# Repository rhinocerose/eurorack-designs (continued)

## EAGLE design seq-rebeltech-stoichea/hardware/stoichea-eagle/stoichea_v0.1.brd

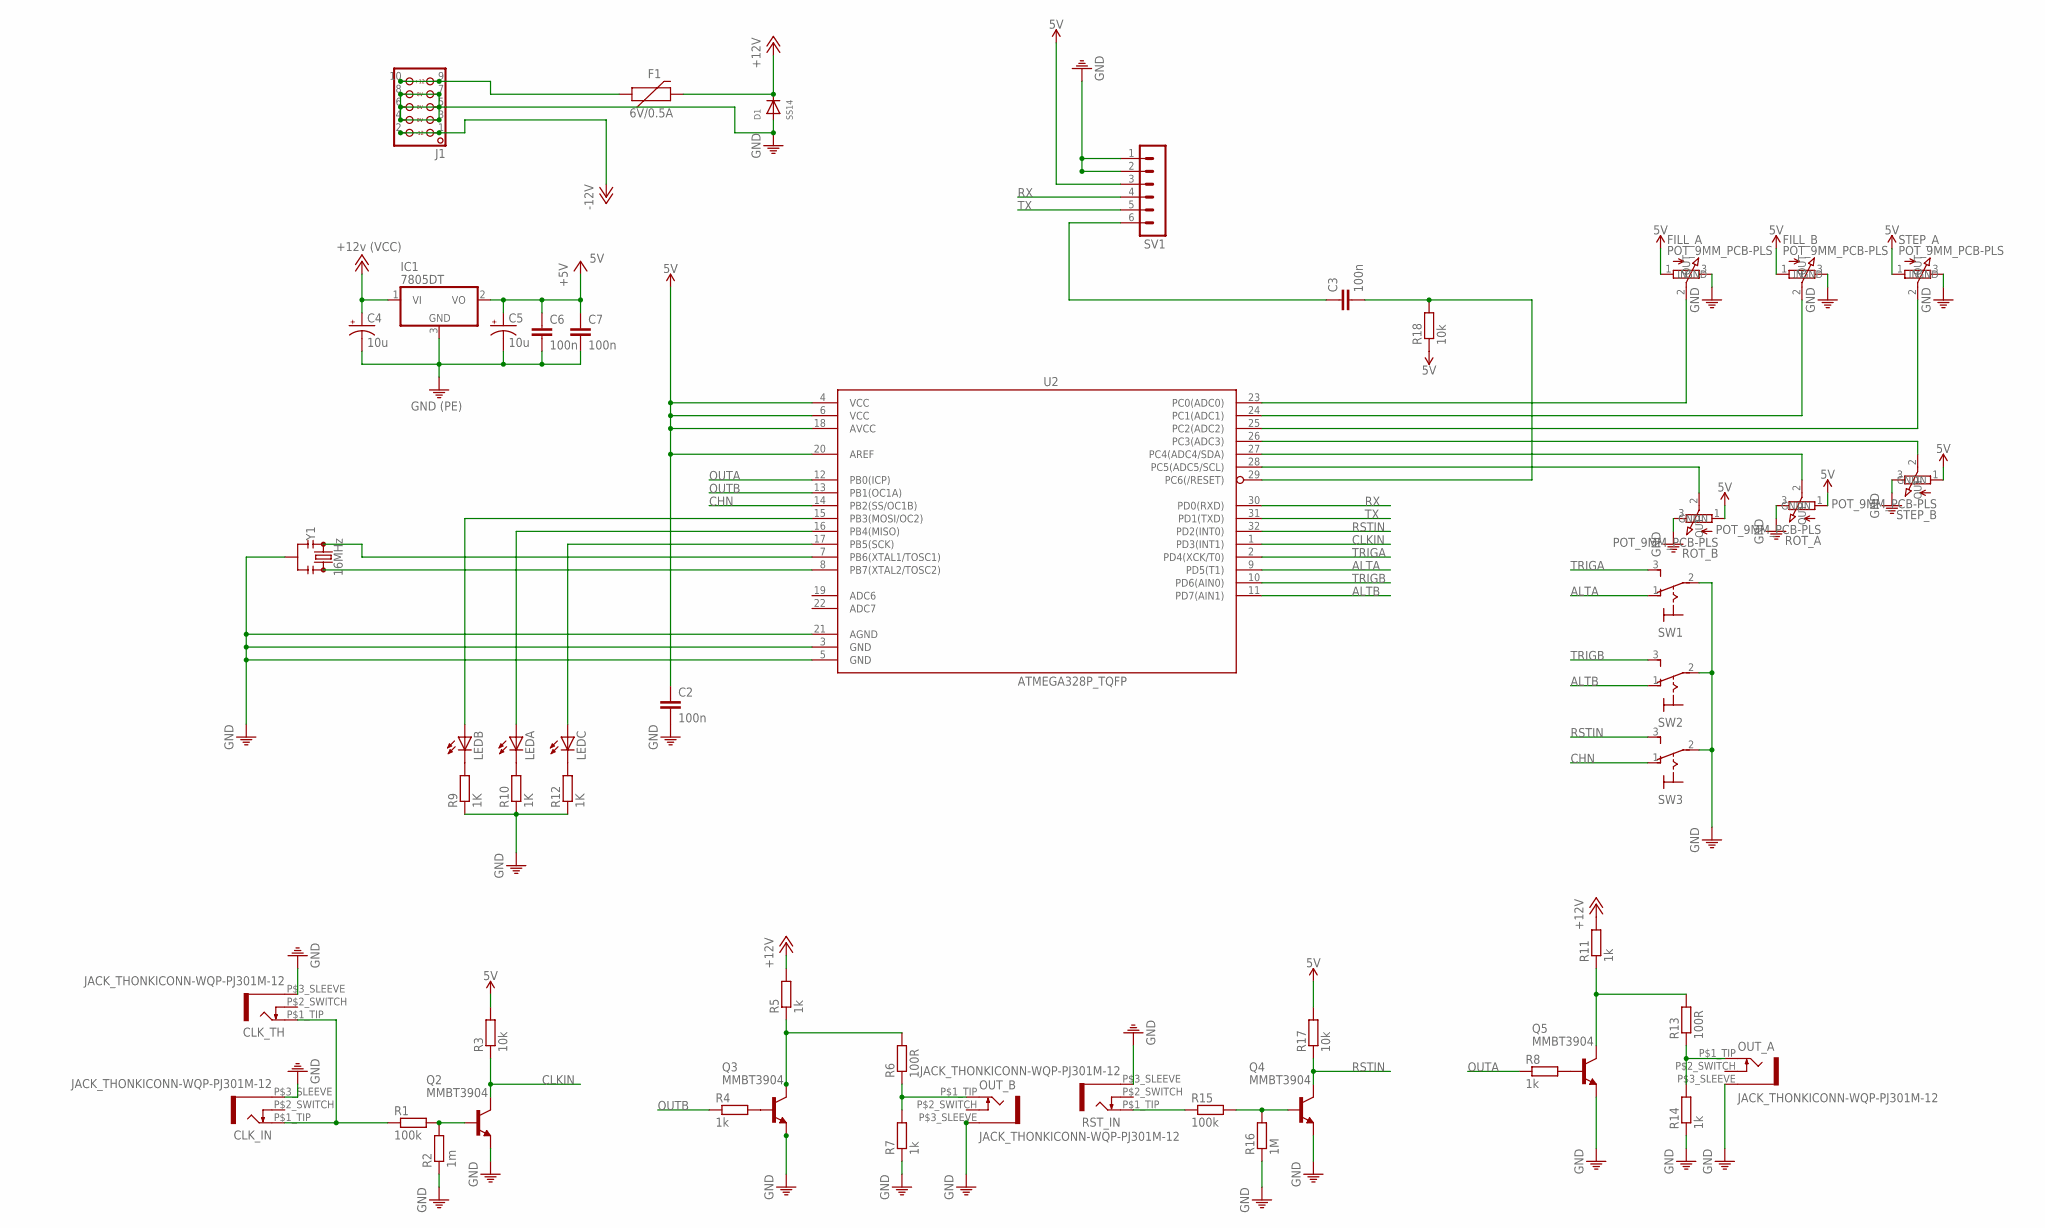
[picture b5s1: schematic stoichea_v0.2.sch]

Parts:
C2, C6, C7: 100n; C0603
C3: 100n; C0603K
C4, C5: 10u; PANASONIC_B
CLK_IN: JACK_THONKICONN-WQP-PJ301M-12; WQP-PJ301M-12_JACK
CLK_TH: JACK_THONKICONN-WQP-PJ301M-12; WQP-PJ301M-12_JACK
D1: SS14; SOD-323F
F1: 6V/0.5A; 1206
FILL_A: POT_9MM_PCB-PLS; 9MM_PLS
FILL_B: POT_9MM_PCB-PLS; 9MM_PLS
IC1: 7805DT; TO252
J1: HEADER-EUROPWR_2X05-OPEN; 2X05_EUROPWR_OPEN
LEDA: LED3MM
LEDB: LED3MM
LEDC: LED3MM
OUT_A: JACK_THONKICONN-WQP-PJ301M-12; WQP-PJ301M-12_JACK
OUT_B: JACK_THONKICONN-WQP-PJ301M-12; WQP-PJ301M-12_JACK
Q2, Q3, Q4, Q5: MMBT3904; SOT23-BEC
R1, R15: 100k; R0603
R2: 1m; R0603
R3, R17, R18: 10k; R0603
R4, R5, R7, R8, R11, R14: 1k; R0603
R6, R13: 100R; R0603
R9, R10, R12: 1K; R0603
R16: 1M; R0603
ROT_A: POT_9MM_PCB-PLS; 9MM_PLS
ROT_B: POT_9MM_PCB-PLS; 9MM_PLS
RST_IN: JACK_THONKICONN-WQP-PJ301M-12; WQP-PJ301M-12_JACK
STEP_A: POT_9MM_PCB-PLS; 9MM_PLS
STEP_B: POT_9MM_PCB-PLS; 9MM_PLS
SV1: MA06-1
SW1, SW2, SW3: SWITCH-SPDT-320-916; 320-916
U2: ATMEGA328P_TQFP; TQFP32-08
Y1: 16MHz; RESONATOR-SMD-3.2X1.3

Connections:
5V: C2.1, C5.+, C6.1, C7.1, FILL_A.1 (GND), FILL_B.1 (GND), IC1.2 (VO), R3.2, R17.2, R18.1, ROT_A.1 (GND), ROT_B.1 (GND), STEP_A.1 (GND), STEP_B.1 (GND), SV1.3, U2.4 (VCC), U2.6 (VCC), U2.18 (AVCC), U2.20 (AREF); also elsewhere on the board
+12V: C4.+, D1.C, F1.2, IC1.1 (VI), R5.2, R11.2; also elsewhere on the board
-12V: J1.1, J1.2
ALTA: SW1.1 (O), U2.9 (PD5(T1))
ALTB: SW2.1 (O), U2.11 (PD7(AIN1))
CHN: SW3.1 (O), U2.14 (PB2(SS/OC1B))
CLKIN: Q2.C, R3.1, U2.1 (PD3(INT1))
unnamed: LEDB.K (C), R9.2
unnamed: LEDA.K (C), R10.2
unnamed: LEDC.K (C), R12.2
unnamed: LEDB.A, U2.15 (PB3(MOSI/OC2))
unnamed: LEDA.A, U2.16 (PB4(MISO))
unnamed: LEDC.A, U2.17 (PB5(SCK))
unnamed: CLK_IN.P$1_TIP (2), CLK_TH.P$1_TIP (2), R1.1
unnamed: F1.1, J1.9, J1.10
unnamed: Q2.B, R1.2, R2.2
unnamed: Q3.B, R4.2
unnamed: Q3.C, R5.1, R6.2
unnamed: OUT_B.P$1_TIP (2), R6.1, R7.2
unnamed: Q5.B, R8.2
unnamed: Q5.C, R11.1, R13.2
unnamed: OUT_A.P$1_TIP (2), R13.1, R14.2
unnamed: R15.1, RST_IN.P$1_TIP (2)
unnamed: C3.2, R18.2, U2.29 (PC6(/RESET))
unnamed: Q4.B, R15.2, R16.2
unnamed: C3.1, SV1.6
unnamed: FILL_A.2 (OUT), U2.23 (PC0(ADC0))
unnamed: FILL_B.2 (OUT), U2.24 (PC1(ADC1))
unnamed: STEP_A.2 (OUT), U2.25 (PC2(ADC2))
unnamed: STEP_B.2 (OUT), U2.26 (PC3(ADC3))
unnamed: ROT_A.2 (OUT), U2.27 (PC4(ADC4/SDA))
unnamed: ROT_B.2 (OUT), U2.28 (PC5(ADC5/SCL))
unnamed: U2.8 (PB7(XTAL2/TOSC2)), Y1.3
unnamed: U2.7 (PB6(XTAL1/TOSC1)), Y1.1
OUTA: R8.1, U2.12 (PB0(ICP))
OUTB: R4.1, U2.13 (PB1(OC1A))
PE: C2.2, C4.-, C5.-, C6.2, C7.2, CLK_IN.P$3_SLEEVE (1), CLK_TH.P$3_SLEEVE (1), D1.A, FILL_A.3 (IN), FILL_B.3 (IN), IC1.3 (GND), J1.3, J1.4, J1.5, J1.6, J1.7, J1.8, OUT_A.P$3_SLEEVE (1), OUT_B.P$3_SLEEVE (1), Q2.E, Q3.E, Q4.E, Q5.E, R2.1, R7.1, R9.1, R10.1, R12.1, R14.1, R16.1, ROT_A.3 (IN), ROT_B.3 (IN), RST_IN.P$3_SLEEVE (1), STEP_A.3 (IN), STEP_B.3 (IN), SV1.1, SV1.2, SW1.2, SW2.2, SW3.2, U2.3 (GND), U2.5 (GND), U2.21 (AGND), Y1.2; also elsewhere on the board
RSTIN: Q4.C, R17.1, SW3.3 (S), U2.32 (PD2(INT0))
RX: SV1.4, U2.30 (PD0(RXD))
TRIGA: SW1.3 (S), U2.2 (PD4(XCK/T0))
TRIGB: SW2.3 (S), U2.10 (PD6(AIN0))
TX: SV1.5, U2.31 (PD1(TXD))

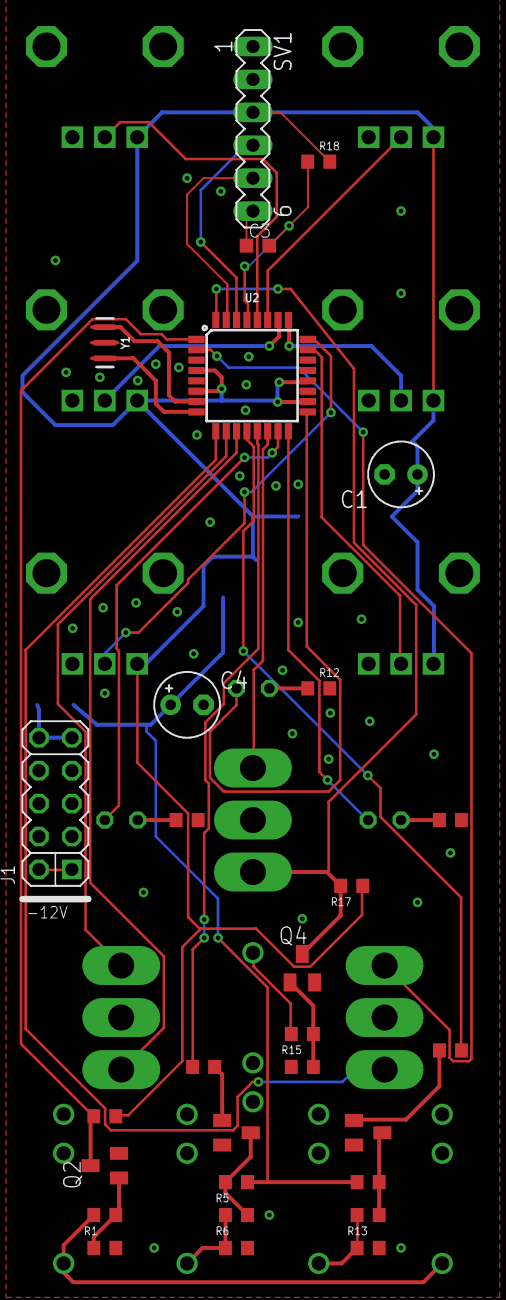
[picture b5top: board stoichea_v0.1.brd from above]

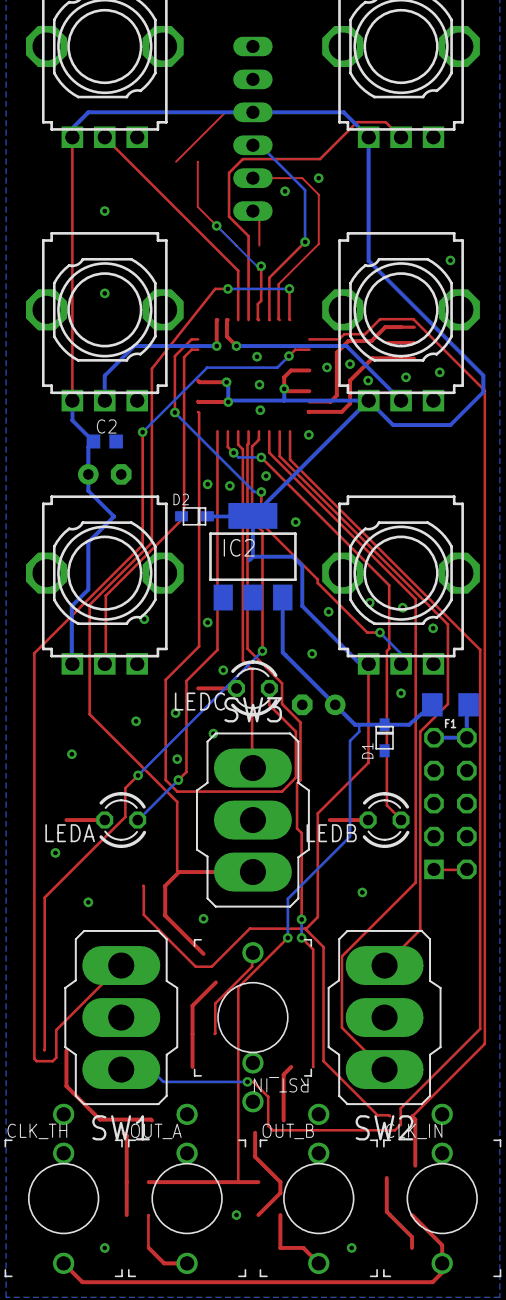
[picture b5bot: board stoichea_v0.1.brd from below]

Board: 2 copper layers, 51 parts (22 on the bottom side), 42 nets.

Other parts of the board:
C1: E2,5-5
D2: 1N4004; SOD-323F
IC2: LD117AS12TR; SOT223

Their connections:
5V: C1.+, D2.C, IC2.4; also elsewhere on the board
+12V: IC2.3; also elsewhere on the board
PE: C1.-, D2.A, IC2.1; also elsewhere on the board

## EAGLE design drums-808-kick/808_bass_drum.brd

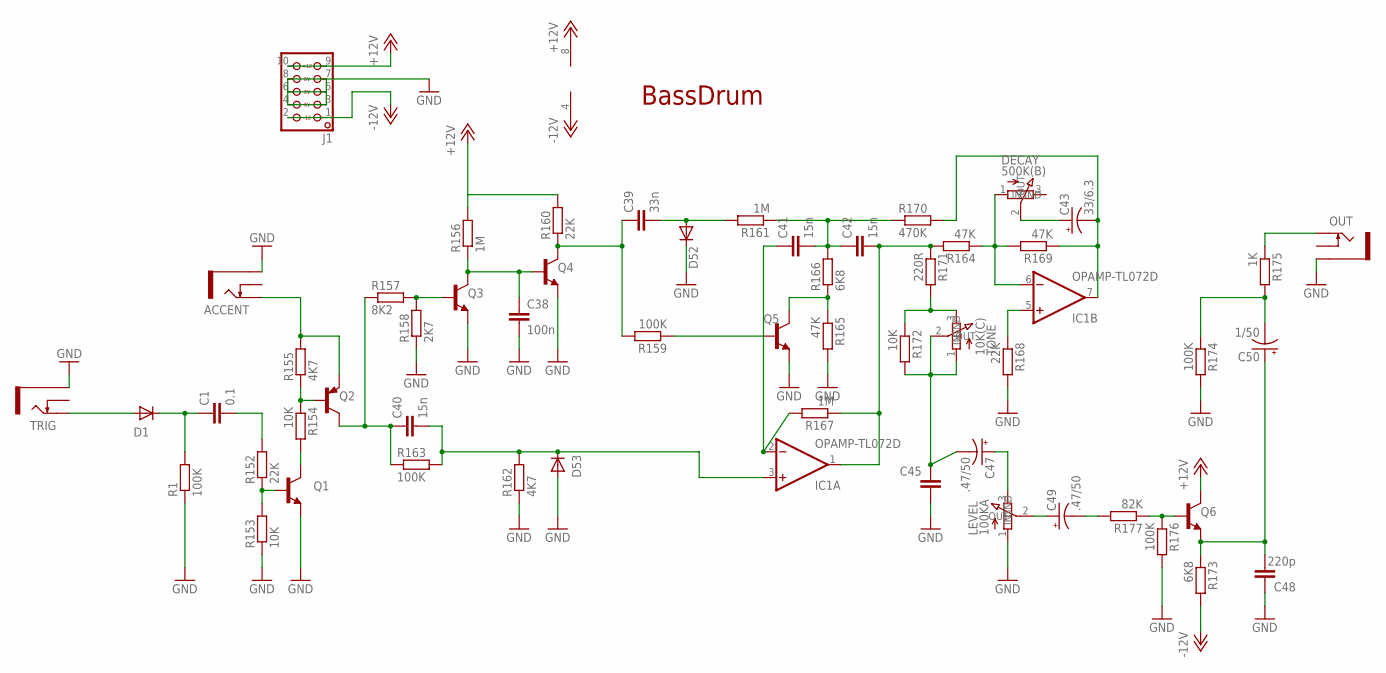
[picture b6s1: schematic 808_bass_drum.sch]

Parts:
ACCENT: JACK_THONKICONNNEW; WQP-PJ301M-12_JACK
C1: 0.1; C0603
C38, C45: 100n; C0603
C39: 33n; C0603
C40, C41, C42: 15n; C0603
C43: 33/6.3; E2,5-5
C47, C49: .47/50; E2,5-5
C48: 220p; C0603
C50: 1/50; E2,5-5
D1, D52, D53: 1N4148; SOD323W_INFINEON
DECAY: 500K(B); 9MM_PLS
IC1: OPAMP-TL072D; SO08
J1: HEADER-EUROPWR_2X05-OPEN; 2X05_EUROPWR_OPEN
LEVEL: 100KA; 9MM_PLS
OUT: JACK_THONKICONNNEW; WQP-PJ301M-12_JACK
Q1, Q3, Q4, Q5, Q6: bc546; SOT23-BEC
Q2: bc556; SOT23-BEC
R1, R159, R163, R174, R176: 100K; R0603
R152, R160, R168: 22K; R0603
R153, R154, R172: 10K; R0603
R155, R162: 4K7; R0603
R156, R161, R167: 1M; R0603
R157: 8K2; R0603
R158: 2K7; R0603
R164, R165, R169: 47K; R0603
R166, R173: 6K8; R0603
R170: 470K; R0603
R171: 220R; R0603
R175: 1K; R0603
R177: 82K; R0603
TONE: 10K(C); 9MM_PLS
TRIG: JACK_THONKICONNNEW; WQP-PJ301M-12_JACK

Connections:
+12V: IC1.8 (V+), J1.9, J1.10, Q6.C, R156.2, R160.2
-12V: IC1.4 (V-), J1.1, J1.2, R173.2
C49: C49.-, R177.2
GND: ACCENT.P$3_SLEEVE (SLEEVE), C38.2, C45.2, C48.1, D52.C, D53.A, J1.3, J1.4, J1.5, J1.6, J1.7, J1.8, LEVEL.1 (GND), OUT.P$3_SLEEVE (SLEEVE), Q1.E, Q3.E, Q4.E, Q5.E, R1.1, R153.1, R158.1, R162.1, R165.2, R168.2, R174.2, R176.2, TRIG.P$3_SLEEVE (SLEEVE)
unnamed: DECAY.1 (GND), IC1.6 (-IN), R164.1, R169.2
unnamed: IC1.5 (+IN), R168.1
unnamed: OUT.P$1_TIP (TIP), R175.1
unnamed: D1.A, TRIG.P$1_TIP (TIP)
unnamed: C1.1, D1.C, R1.2
unnamed: C1.2, R152.2
unnamed: C38.1, Q3.C, Q4.B, R156.1
unnamed: Q2.B, R154.1, R155.1
unnamed: Q5.C, R165.1, R166.1
unnamed: Q3.B, R157.2, R158.2
unnamed: Q1.C, R154.2
unnamed: C39.1, Q4.C, R159.2, R160.1
unnamed: C40.1, Q2.C, R157.1, R163.1
unnamed: C40.2, D53.C, IC1.3 (+IN), R162.2, R163.2
unnamed: Q5.B, R159.1
unnamed: C41.2, C42.1, R161.1, R166.2, R170.1
unnamed: C41.1, IC1.2 (-IN), R167.2
unnamed: C42.2, IC1.1 (OUT), R164.2, R167.1, R171.1
unnamed: C45.1, C47.-, R172.2, TONE.1 (GND), TONE.2 (OUT)
unnamed: R171.2, R172.1, TONE.3 (IN)
unnamed: C43.-, IC1.7 (OUT), R169.1, R170.2
unnamed: Q6.B, R176.1, R177.1
unnamed: C48.2, C50.+, Q6.E, R173.1
unnamed: C50.-, R174.1, R175.2
unnamed: C47.+, LEVEL.3 (IN)
unnamed: C49.+, LEVEL.2 (OUT)
unnamed: C43.+, DECAY.2 (OUT)
unnamed: Q1.B, R152.1, R153.2
unnamed: C39.2, D52.A, R161.2
TRIG: ACCENT.P$1_TIP (TIP), Q2.E, R155.2

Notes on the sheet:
BassDrum

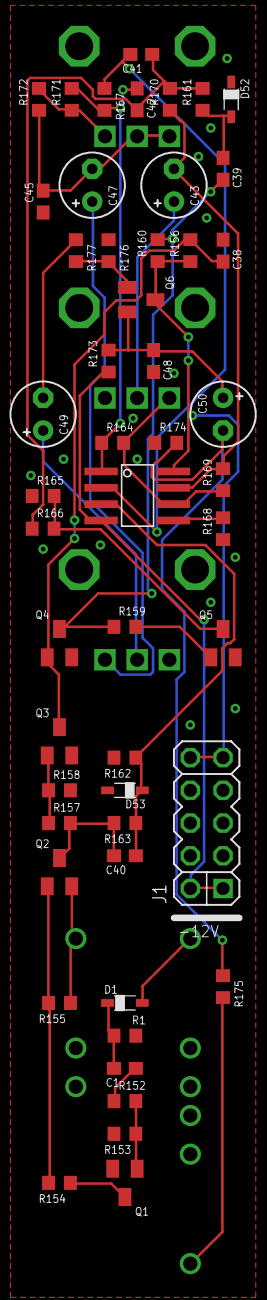
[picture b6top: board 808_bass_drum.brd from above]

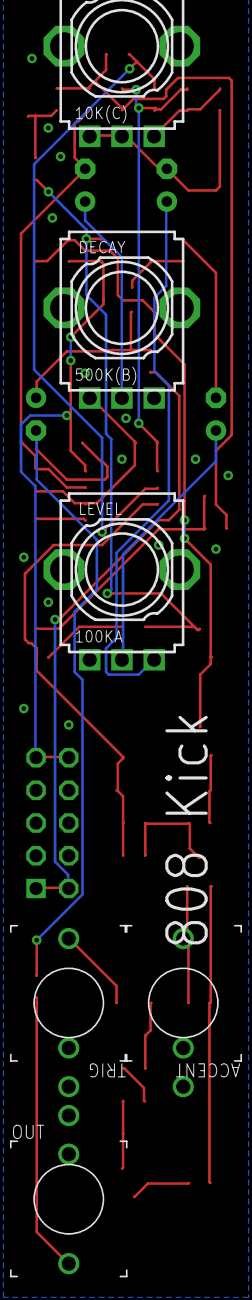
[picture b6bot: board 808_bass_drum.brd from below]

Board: 2 copper layers, 56 parts (6 on the bottom side), 34 nets.

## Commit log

2022-04-20 Fully working!!
2025-08-12 909-work
2025-08-12 Update submodules to track main branch
2025-08-12 Update submodules: set branch=main and fix URLs
2025-08-12 Update submodules: add branch=main and fix URLs
2025-08-13 Remove .gitmodules (no submodules exist)
